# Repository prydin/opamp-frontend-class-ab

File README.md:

# The Teamwork Amplifier - 50W (8 ohm) Low Distortion Class AB Audio Amplifier

## Background
This is a team effort that started as a conversation on diyaudio.com. Member stigigemla and I were bouncing ideas back and forth and member steveu took one my design
attempts and came up with an overhauled and much improved version. I just added some extra features like overcurrent protecton and VI limiters and slapped together a PCB. 
I built it as an experiment.

The result is a fast amplifier (>80V/us slew rate) with low distortion (0.00045% meadured @ 1kHz/1W/8ohm resistive load). It's undergone some preliminary measurements
and looks quite promising. 

## Disclaimer
The schematic and PCB layout are free to use as you please, but bear in mind that it's only undergone a bare minimum of testing! Build at your own risk!

## Credits and acknowledgements
There were several people involved in the creation of this design. If you're not mentioned and feel you should be, just add your name and issue a PR! 

## Schematic

## PCB 3D rendering

## Measurements
- THD: 0.00045% @ 1W/1kHz/150mA bias
- SNR: >95dB
- Bandwidth: 10Hz-500kHz
- Slew rate: >80V/us

## Subjective listening impression
After a few hours of listening, I have to say I'm pleased with the sound quality. It character is very crisp and clean. Drum beats and cymbals feel very snappy. 
If you're looking for an amplifierthat colors the sound, this won't be your cup of tea. But so far I would say it does a great job at cleanly reproducing the source material. 

## Construction
I found an old, broken AudioSource Amp 100 on eBay for close to no money and reused the chassis, pots, connectors and transformer. The boards ended up fitting perfectly if
I moved the heatsink maybe 3mm back and removed the input switching board (which I didn't want or need anyway). It ended up being a neat and inexpensive build
that looks sleek and clean.

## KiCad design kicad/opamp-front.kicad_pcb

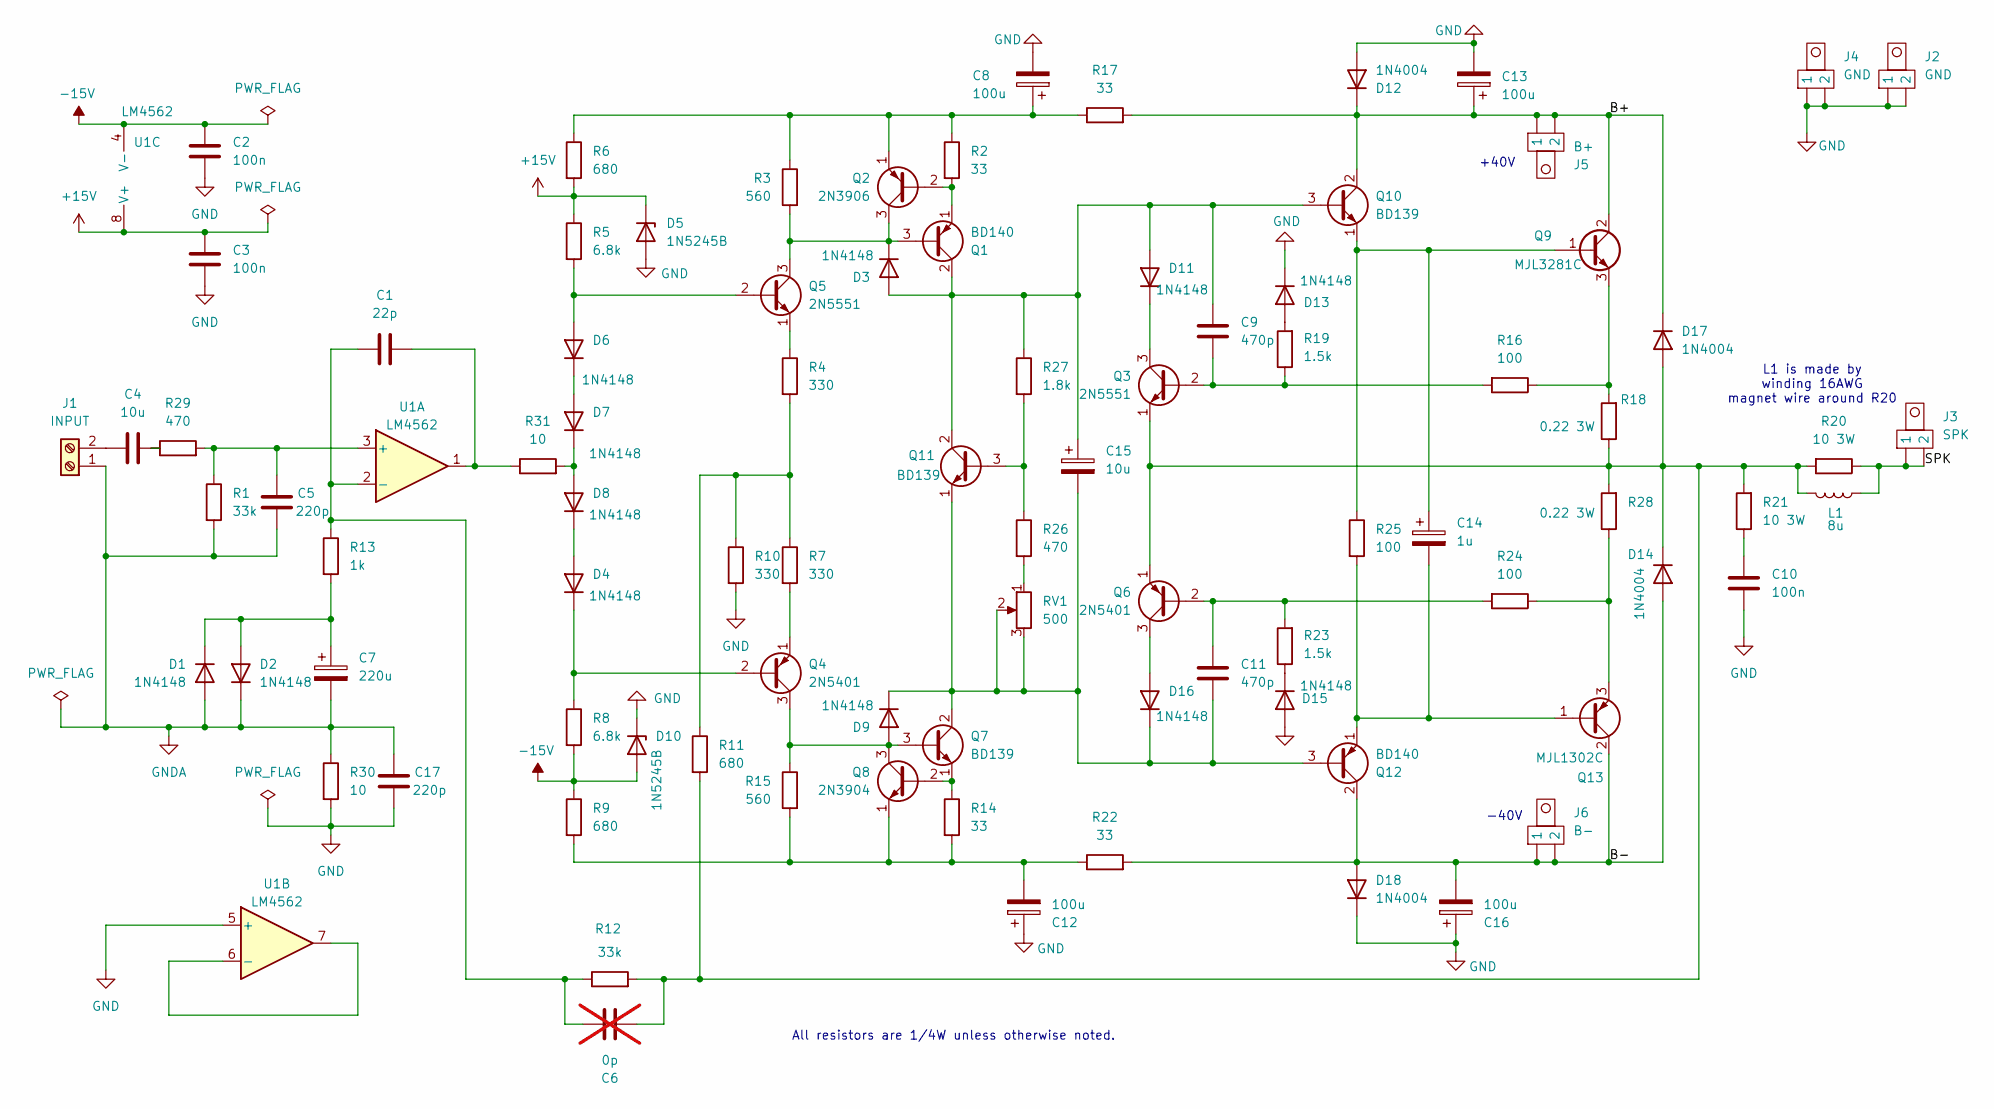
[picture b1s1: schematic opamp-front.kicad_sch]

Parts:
C1: 22p; C_Rect_L7.2mm_W3.0mm_P5.00mm_FKS2_FKP2_MKS2_MKP2
C2, C3, C10: 100n; C_Rect_L7.2mm_W3.0mm_P5.00mm_FKS2_FKP2_MKS2_MKP2
C4, C15: 10u; CP_Radial_D4.0mm_P2.00mm
C5, C17: 220p; C_Rect_L7.2mm_W3.0mm_P5.00mm_FKS2_FKP2_MKS2_MKP2
C6: 0p; C_Rect_L7.2mm_W3.0mm_P5.00mm_FKS2_FKP2_MKS2_MKP2; not fitted
C7: 220u; CP_Radial_D8.0mm_P5.00mm
C8, C12, C13, C16: 100u; CP_Radial_D8.0mm_P5.00mm
C9, C11: 470p; C_Rect_L7.2mm_W3.0mm_P5.00mm_FKS2_FKP2_MKS2_MKP2
C14: 1u; CP_Radial_D4.0mm_P2.00mm
D1, D2, D3, D4, D6, D7, D8, D9, D11, D13, D15, D16: 1N4148; D_DO-35_SOD27_P7.62mm_Horizontal
D5, D10: 1N5245B; D_DO-35_SOD27_P7.62mm_Horizontal
D12, D14, D17, D18: 1N4004; D_DO-41_SOD81_P10.16mm_Horizontal
J1: INPUT; TerminalBlock_4Ucon_1x02_P3.50mm_Horizontal
J2, J4: GND; Spade Connector
J3: SPK; Spade Connector
J5: B+; Spade Connector
J6: B-; Spade Connector
L1: 8u
Q1, Q12: BD140; TO-126-3_Vertical
Q2: 2N3906; TO-92_HandSolder
Q3, Q5: 2N5551; TO-92_HandSolder
Q4, Q6: 2N5401; TO-92_HandSolder
Q7, Q10, Q11: BD139; TO-126-3_Vertical
Q8: 2N3904; TO-92_HandSolder
Q9: MJL3281C; TO-264-3_Vertical
Q13: MJL1302C; TO-264-3_Vertical
R1, R12: 33k; R_Axial_DIN0204_L3.6mm_D1.6mm_P7.62mm_Horizontal_HandSolder
R2, R14, R17, R22: 33; R_Axial_DIN0204_L3.6mm_D1.6mm_P7.62mm_Horizontal_HandSolder
R3, R15: 560; R_Axial_DIN0204_L3.6mm_D1.6mm_P7.62mm_Horizontal_HandSolder
R4, R7, R10: 330; R_Axial_DIN0204_L3.6mm_D1.6mm_P7.62mm_Horizontal_HandSolder
R5, R8: 6.8k; R_Axial_DIN0204_L3.6mm_D1.6mm_P7.62mm_Horizontal_HandSolder
R6, R9, R11: 680; R_Axial_DIN0204_L3.6mm_D1.6mm_P7.62mm_Horizontal_HandSolder
R13: 1k; R_Axial_DIN0204_L3.6mm_D1.6mm_P7.62mm_Horizontal_HandSolder
R16, R24, R25: 100; R_Axial_DIN0204_L3.6mm_D1.6mm_P7.62mm_Horizontal_HandSolder
R18, R28: 0.22 3W; R_Axial_DIN0411_L9.9mm_D3.6mm_P15.24mm_Horizontal
R19, R23: 1.5k; R_Axial_DIN0204_L3.6mm_D1.6mm_P7.62mm_Horizontal_HandSolder
R20, R21: 10 3W; R_Axial_DIN0411_L9.9mm_D3.6mm_P15.24mm_Horizontal
R26, R29: 470; R_Axial_DIN0204_L3.6mm_D1.6mm_P7.62mm_Horizontal_HandSolder
R27: 1.8k; R_Axial_DIN0204_L3.6mm_D1.6mm_P7.62mm_Horizontal_HandSolder
R30, R31: 10; R_Axial_DIN0204_L3.6mm_D1.6mm_P7.62mm_Horizontal_HandSolder
RV1: 500; TRIM_T93YA103KT20
U1: LM4562; DIP-8_W7.62mm

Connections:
+15V: C3.2, D5.1 (K), R5.1, R6.2, U1.8 (V+)
-15V: C2.2, D10.2 (A), R8.2, R9.1, U1.4 (V-)
/B+: C13.1, D12.1 (K), D17.1 (K), J5.1, J5.2, Q9.2 (C), Q10.2 (C), R17.2
/B-: C16.2, D14.2 (A), D18.2 (A), J6.1, J6.2, Q12.2 (C), Q13.2 (C), R22.2
/SPK: J3.1, J3.2, L1.2, R20.1
GND: C2.1, C3.1, C8.2, C10.1, C12.1, C13.2, C16.1, C17.2, D5.2 (A), D10.1 (K), D12.2 (A), D13.1 (K), D15.2 (A), D18.1 (K), J2.1, J2.2, J4.1, J4.2, R10.2, R30.2, U1.5 (+)
GNDA: C5.2, C7.2, C17.1, D1.2 (A), D2.1 (K), J1.1, R1.2, R30.1
unnamed: C1.2, R31.1, U1.1
unnamed: C4.2, R29.1
unnamed: C10.2, R21.1
unnamed: C7.1, D1.1 (K), D2.2 (A), R13.2
unnamed: D3.1 (K), Q1.3 (B), Q2.3 (C), Q5.3 (C), R3.2
unnamed: D4.2 (A), D8.1 (K)
unnamed: D4.1 (K), Q4.2 (B), R8.1
unnamed: D6.2 (A), Q5.2 (B), R5.2
unnamed: D6.1 (K), D7.2 (A)
unnamed: D7.1 (K), D8.2 (A), R31.2
unnamed: D9.2 (A), Q4.3 (C), Q7.3 (B), Q8.3 (C), R15.1
unnamed: C9.2, C15.1, D3.2 (A), D11.2 (A), Q1.2 (C), Q10.3 (B), Q11.2 (C), R27.1
unnamed: D11.1 (K), Q3.3 (C)
unnamed: D13.2 (A), R19.2
unnamed: C6.2, D14.1 (K), D17.2 (A), L1.1, Q3.1 (E), Q6.1 (E), R11.2, R12.2, R18.1, R20.2, R21.2, R28.2
unnamed: D15.1 (K), R23.1
unnamed: D16.2 (A), Q6.3 (C)
unnamed: C11.1, C15.2, D9.1 (K), D16.1 (K), Q7.2 (C), Q11.1 (E), Q12.3 (B), RV1.2, RV1.3
unnamed: C4.1, J1.2
unnamed: Q1.1 (E), Q2.2 (B), R2.2
unnamed: C8.1, Q2.1 (E), R2.1, R3.1, R6.1, R17.1
unnamed: C9.1, Q3.2 (B), R16.2, R19.1
unnamed: Q4.1 (E), R7.2
unnamed: Q5.1 (E), R4.1
unnamed: C11.2, Q6.2 (B), R23.2, R24.2
unnamed: Q7.1 (E), Q8.2 (B), R14.1
unnamed: C12.2, Q8.1 (E), R9.2, R14.2, R15.2, R22.1
unnamed: Q9.3 (E), R16.1, R18.2
unnamed: C14.1, Q9.1 (B), Q10.1 (E), R25.1
unnamed: Q11.3 (B), R26.1, R27.2
unnamed: C14.2, Q12.1 (E), Q13.1 (B), R25.2
unnamed: Q13.3 (E), R24.1, R28.1
unnamed: R4.2, R7.1, R10.1, R11.1
unnamed: R26.2, RV1.1
unnamed: C5.1, R1.1, R29.2, U1.3 (+)
unnamed: C1.1, C6.1, R12.1, R13.1, U1.2 (-)
unnamed: U1.6 (-), U1.7

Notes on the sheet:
-40V
+40V
L1 is made by winding 16AWG magnet wire around R20
All resistors are 1/4W unless otherwise noted.

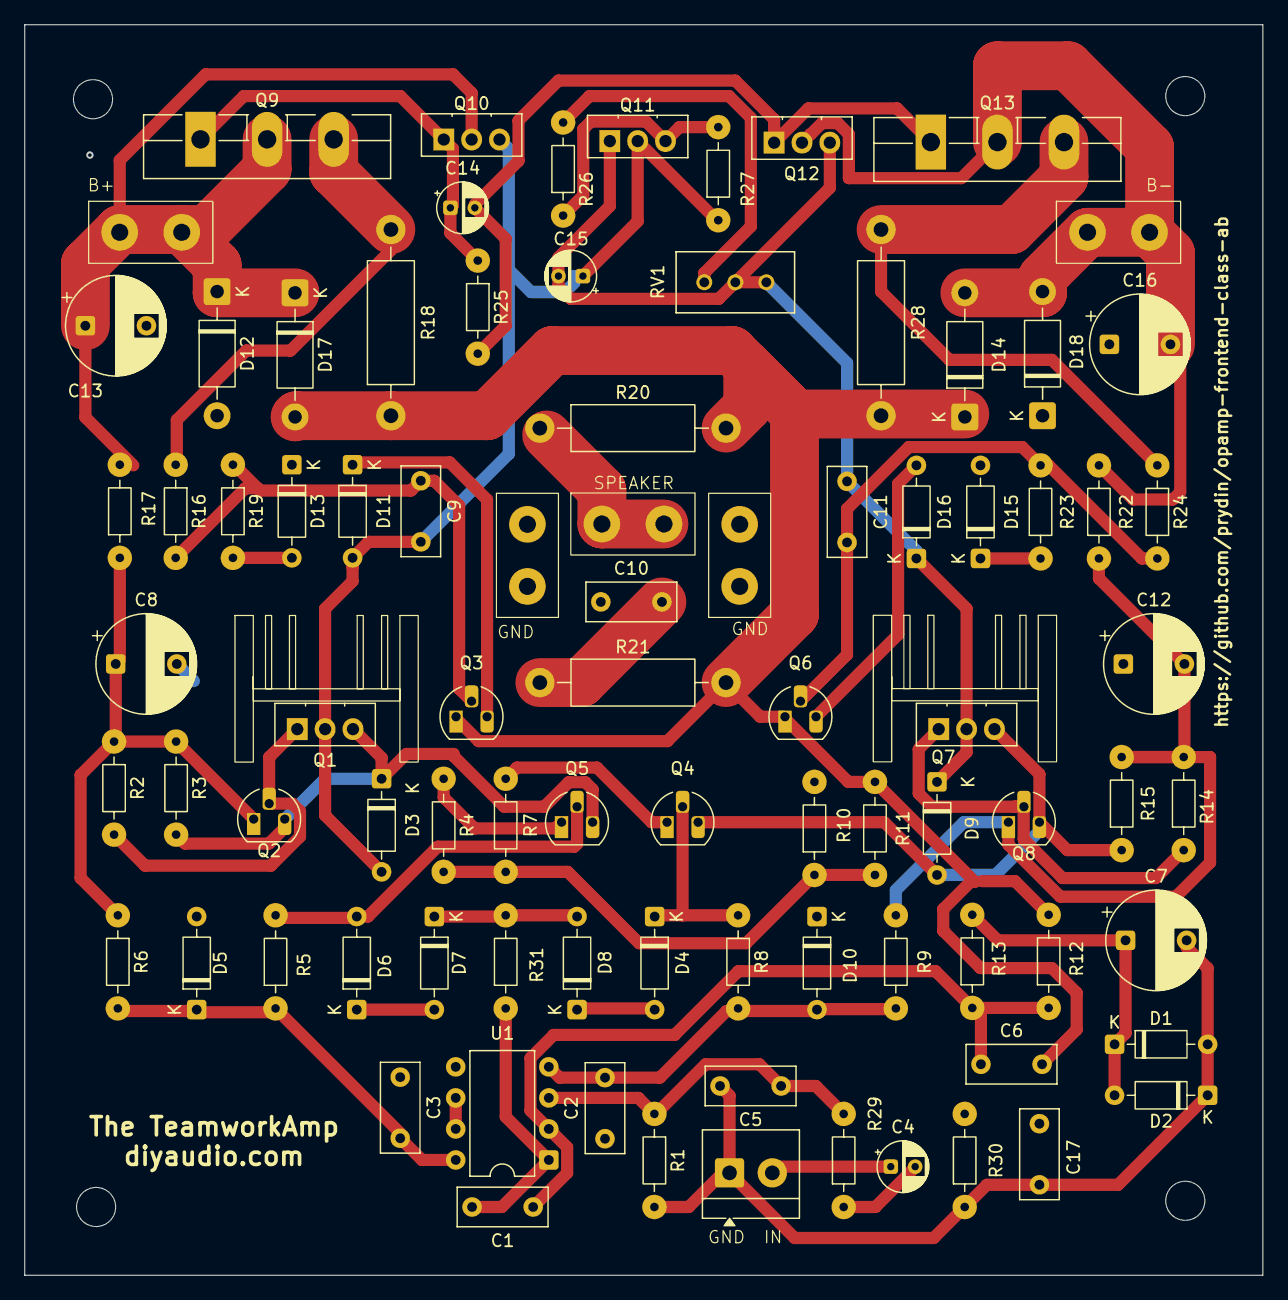
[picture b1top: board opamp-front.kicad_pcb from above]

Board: 2 copper layers, 101.3 x 102.4 mm, 87 parts (0 on the bottom side), 44 nets.

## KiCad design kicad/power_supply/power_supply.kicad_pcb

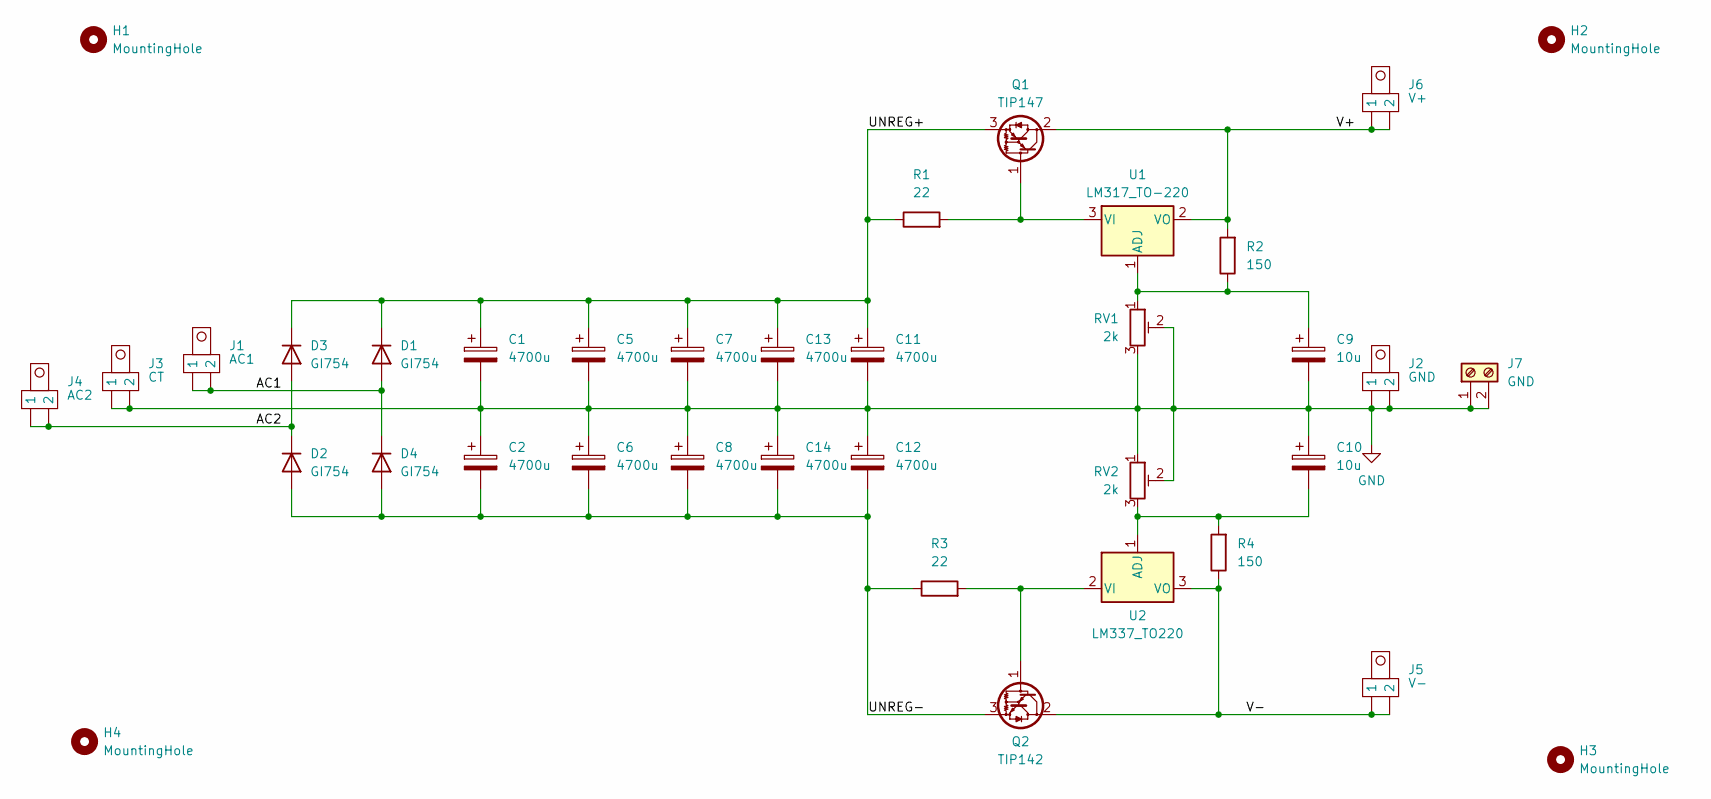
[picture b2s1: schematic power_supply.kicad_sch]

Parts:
C1, C2, C5, C6, C7, C8, C11, C12, C13, C14: 4700u; CP_Radial_D18.0mm_P7.50mm
C9, C10: 10u; CP_Radial_D4.0mm_P2.00mm
D1, D2, D3, D4: GI754; D_P600_R-6_P12.70mm_Horizontal
H1, H2, H3, H4: MountingHole; MountingHole_3.2mm_M3
J1: AC1; Spade Connector
J2: GND; Spade Connector
J3: CT; Spade Connector
J4: AC2; Spade Connector
J5: V-; Spade Connector
J6: V+; Spade Connector
J7: GND; TerminalBlock_Phoenix_MKDS-1,5-2_1x02_P5.00mm_Horizontal
Q1: TIP147; TO-247-3_Horizontal_TabDown
Q2: TIP142; TO-247-3_Horizontal_TabDown
R1, R3: 22; R_Axial_DIN0204_L3.6mm_D1.6mm_P7.62mm_Horizontal
R2, R4: 150; R_Axial_DIN0204_L3.6mm_D1.6mm_P7.62mm_Horizontal
RV1, RV2: 2k; TRIM_T93YA103KT20
U1: LM317_TO-220; TO-220-3_Vertical
U2: LM337_TO220; TO-220-3_Vertical

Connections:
/AC1: D1.2 (A), D4.1 (K), J1.1, J1.2
/AC2: D2.1 (K), D3.2 (A), J4.1, J4.2
/UNREG+: C1.1, C5.1, C7.1, C11.1, C13.1, D1.1 (K), D3.1 (K), Q1.3 (E), R1.1
/UNREG-: C2.2, C6.2, C8.2, C12.2, C14.2, D2.2 (A), D4.2 (A), Q2.3 (E), R3.1
/V+: J6.1, J6.2, Q1.2 (C), R2.2, U1.2 (VO); also elsewhere on the board
/V-: J5.1, J5.2, Q2.2 (C), R4.1, U2.3 (VO); also elsewhere on the board
GND: C1.2, C2.1, C5.2, C6.1, C7.2, C8.1, C9.2, C10.1, C11.2, C12.1, C13.2, C14.1, J2.1, J2.2, J3.1, J3.2, J7.1, J7.2, RV1.2, RV1.3, RV2.1, RV2.2; also elsewhere on the board
unnamed: Q1.1 (B), R1.2, U1.3 (VI)
unnamed: Q2.1 (B), R3.2, U2.2 (VI)
unnamed: C9.1, R2.1, RV1.1, U1.1 (ADJ)
unnamed: C10.2, R4.2, RV2.3, U2.1 (ADJ)

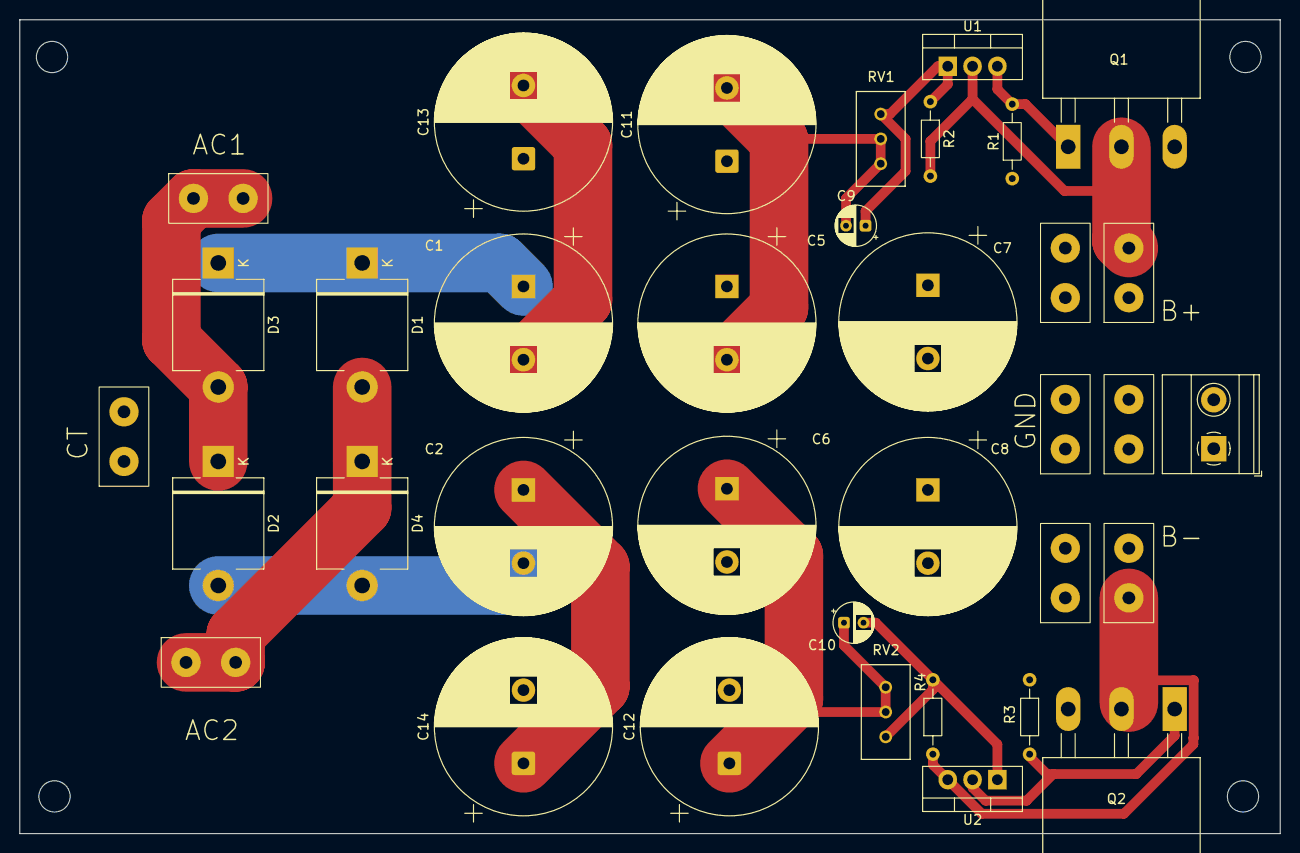
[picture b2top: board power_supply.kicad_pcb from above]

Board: 2 copper layers, 129.0 x 83.3 mm, 40 parts (0 on the bottom side), 11 nets.

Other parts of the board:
J3#2: CT; Spade Connector
J5#2: V-; Spade Connector
J6#2: V+; Spade Connector

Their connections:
/V+: J6#2.1, J6#2.2; also elsewhere on the board
/V-: J5#2.1, J5#2.2; also elsewhere on the board
GND: J3#2.1, J3#2.2; also elsewhere on the board

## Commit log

2025-11-10 Moved things a bit
2025-11-13 Gerbers generated
2025-11-23 Preparing for public release
2025-11-23 Restored after rebase mishap
2025-11-24 Release 1.0
2025-11-24 Cleaned up
2025-11-24 Add initial README for Teamwork Amplifier project
2025-11-24 Add credits and acknowledgements section to README
    Added credits section to acknowledge contributors.
2025-11-24 Fix typo in credits section of README
2025-11-27 PCB improvments and lineup's adjustments.
2025-11-27 Cosmetic adjustments
2025-12-04 Release candidate 1
2025-12-04 Add Measurements section to README
    Added a section for measurements with preliminary data.
2025-12-04 Revise README with updated amplifier specifications
    Updated performance metrics and added subjective listening impressions and construction details.
2025-12-04 Remove duplicate measurements from README
    Removed duplicate measurements section in README.
2025-12-05 Fix typo in README.md
    Corrected a typo in the subjective listening impression section.
